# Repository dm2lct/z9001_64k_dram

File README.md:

# z9001_64k_dram
64kB RAM Modul für den Robotron KC87

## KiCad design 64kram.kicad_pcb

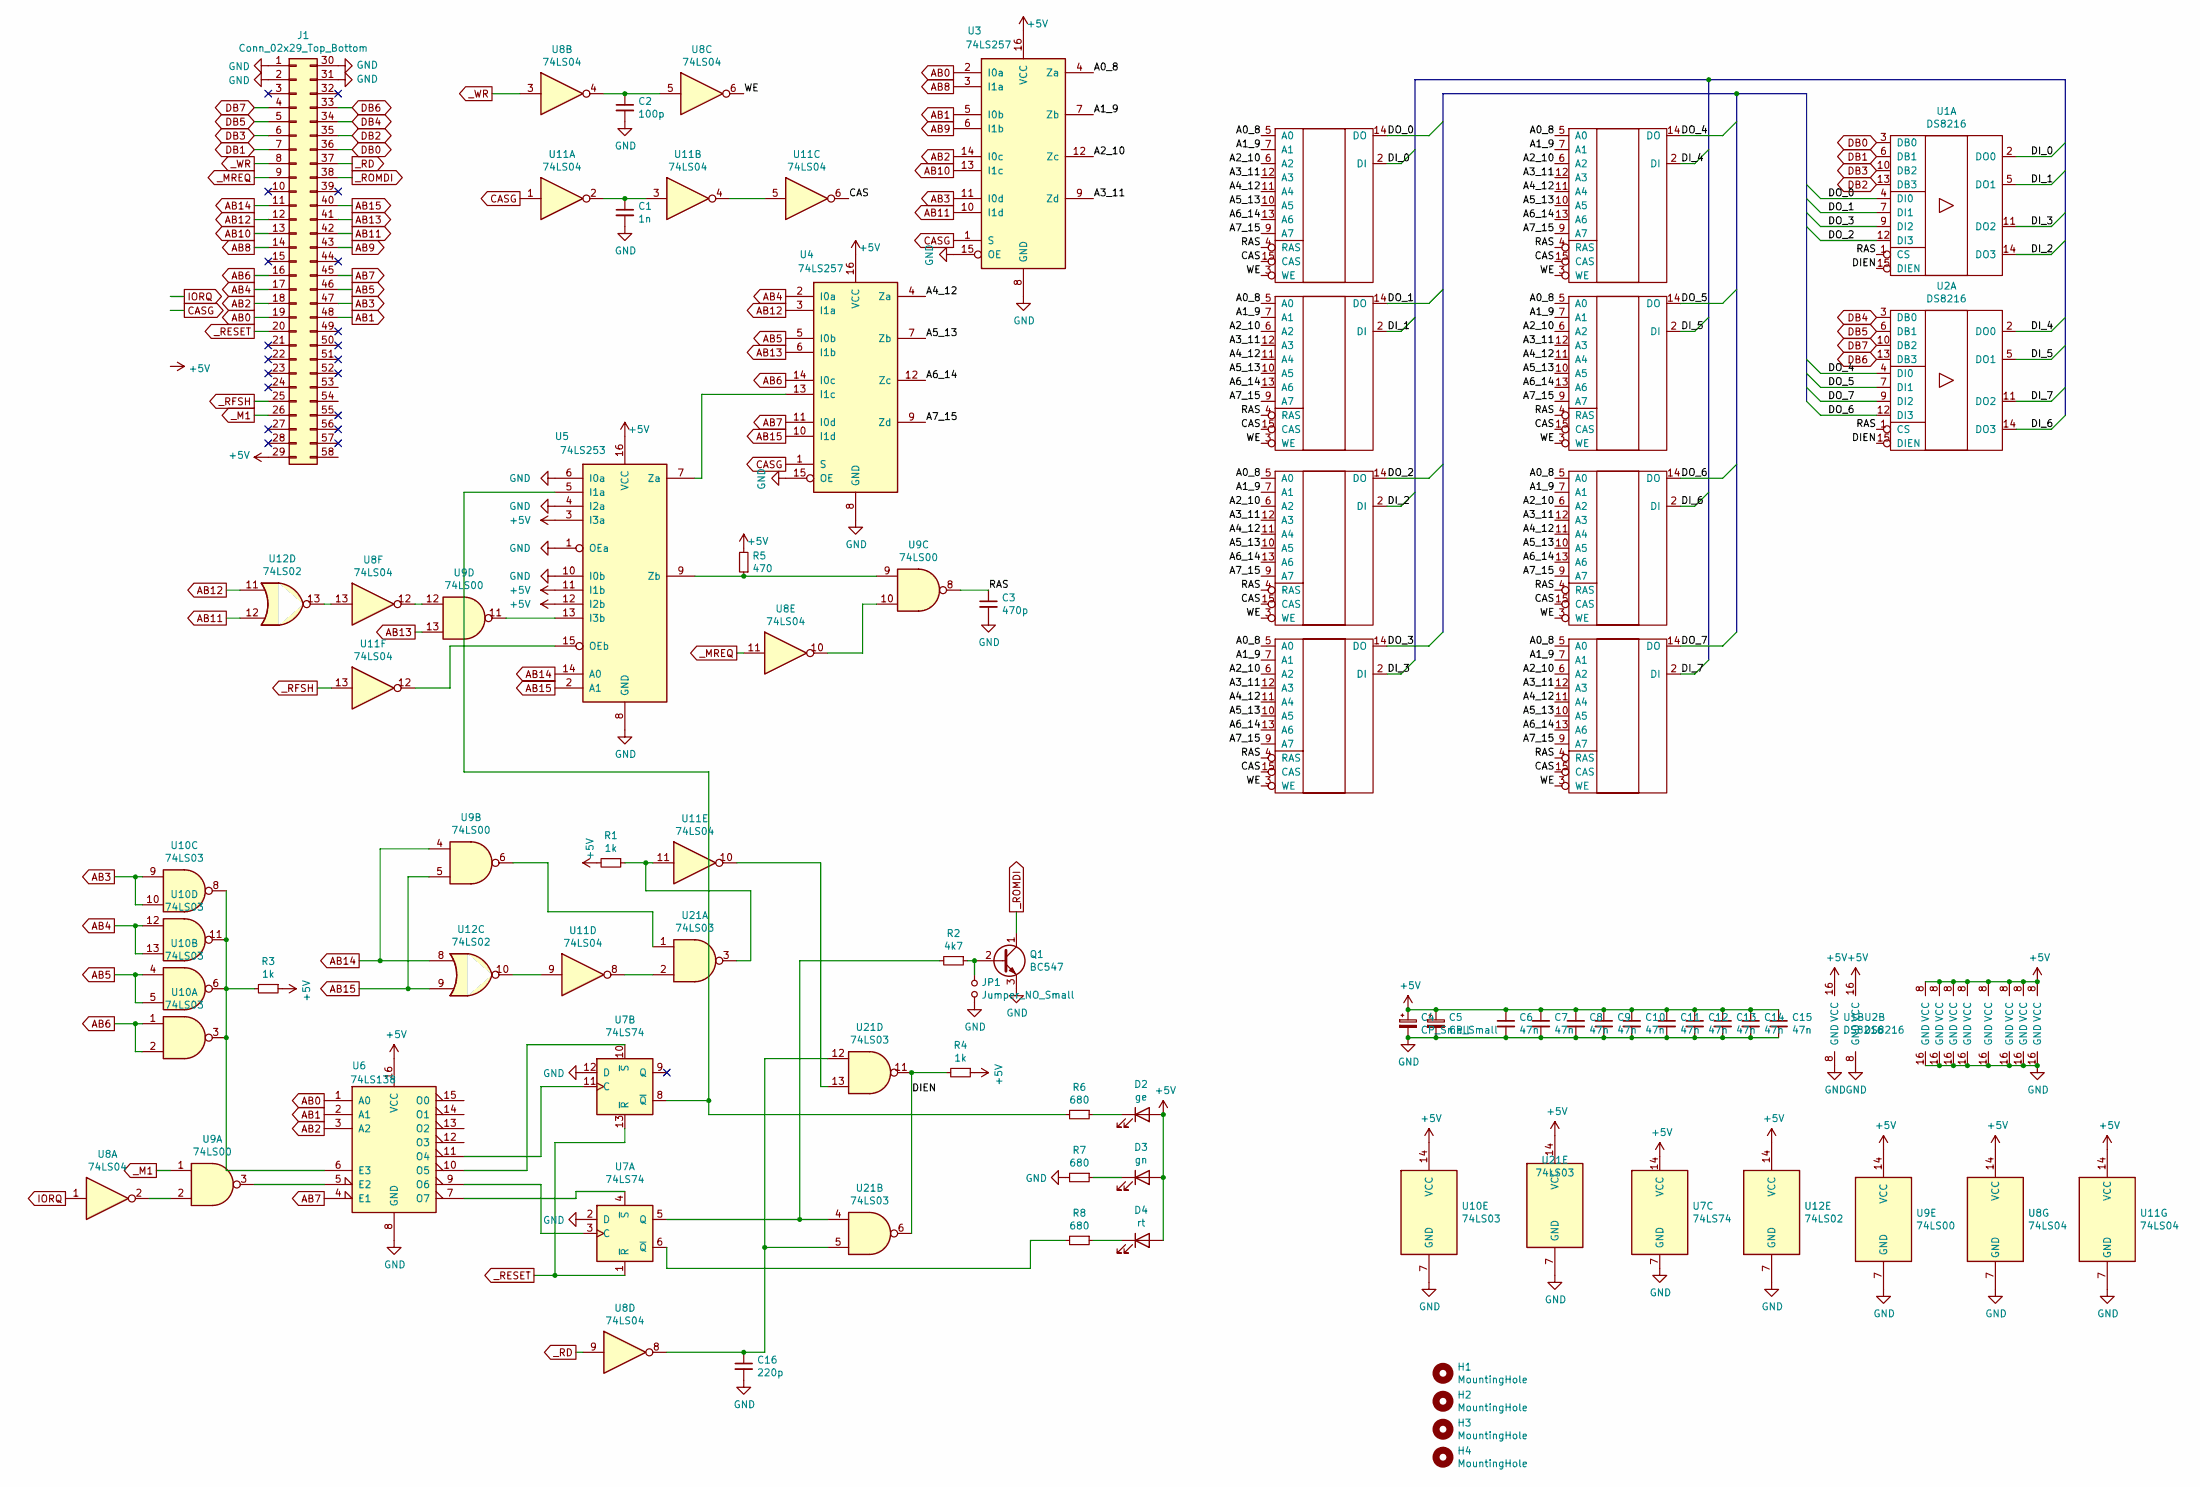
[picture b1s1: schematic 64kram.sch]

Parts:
C1: 1n; C_Disc_D4.3mm_W1.9mm_P5.00mm
C2: 100p; C_Disc_D4.3mm_W1.9mm_P5.00mm
C3: 470p; C_Disc_D4.3mm_W1.9mm_P5.00mm
C4, C5: CP_Small; CP_Axial_L11.0mm_D5.0mm_P18.00mm_Horizontal
C6, C7, C8, C9, C10, C11, C12, C13, C14, C15: 47n; C_Disc_D4.3mm_W1.9mm_P5.00mm
C16: 220p; C_Disc_D4.3mm_W1.9mm_P5.00mm
D2: ge; LED_D3.0mm
D3: gn; LED_D3.0mm
D4: rt; LED_D3.0mm
H1, H2, H3, H4: MountingHole; MountingHole_4.3mm_M4_DIN965
J1: Conn_02x29_Top_Bottom; EFS_58
JP1: Jumper_NO_Small; PinHeader_1x02_P2.54mm_Vertical
Q1: BC547; TO-92_Inline
R1, R3, R4: 1k; R_Axial_DIN0204_L3.6mm_D1.6mm_P7.62mm_Horizontal
R2: 4k7; R_Axial_DIN0204_L3.6mm_D1.6mm_P7.62mm_Horizontal
R5: 470; R_Axial_DIN0204_L3.6mm_D1.6mm_P7.62mm_Horizontal
R6, R7, R8: 680; R_Axial_DIN0204_L3.6mm_D1.6mm_P7.62mm_Horizontal
U1, U2: DS8216; DIP-16_W7.62mm
U3, U4: 74LS257; DIP-16_W7.62mm
U5: 74LS253; DIP-16_W7.62mm
U6: 74LS138; DIP-16_W7.62mm
U7: 74LS74; DIP-14_W7.62mm
U8, U11: 74LS04; DIP-14_W7.62mm
U9: 74LS00; DIP-14_W7.62mm
U10, U21: 74LS03; DIP-14_W7.62mm
U12: 74LS02; DIP-14_W7.62mm
U13, U14, U15, U16, U17, U18, U19, U20: U2164; DIP-16_W7.62mm

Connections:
+5V: C4.1, C5.1, C6.1, C7.1, C8.1, C9.1, C10.1, C11.1, C12.1, C13.1, C14.1, C15.1, D2.2 (A), D3.2 (A), D4.2 (A), J1.29, J1.58, R1.2, R3.1, R4.1, R5.2, U1.16 (VCC), U2.16 (VCC), U3.16 (VCC), U4.16 (VCC), U5.3 (I3a), U5.11 (I1b), U5.12 (I2b), U5.16 (VCC), U6.16 (VCC), U7.14 (VCC), U8.14 (VCC), U9.14 (VCC), U10.14 (VCC), U11.14 (VCC), U12.14 (VCC), U13.8 (VCC), U14.8 (VCC), U15.8 (VCC), U16.8 (VCC), U17.8 (VCC), U18.8 (VCC), U19.8 (VCC), U20.8 (VCC), U21.14 (VCC)
/A0_8: U3.4 (Za), U13.5 (A0), U14.5 (A0), U15.5 (A0), U16.5 (A0), U17.5 (A0), U18.5 (A0), U19.5 (A0), U20.5 (A0)
/A1_9: U3.7 (Zb), U13.7 (A1), U14.7 (A1), U15.7 (A1), U16.7 (A1), U17.7 (A1), U18.7 (A1), U19.7 (A1), U20.7 (A1)
/A2_10: U3.12 (Zc), U13.6 (A2), U14.6 (A2), U15.6 (A2), U16.6 (A2), U17.6 (A2), U18.6 (A2), U19.6 (A2), U20.6 (A2)
/A3_11: U3.9 (Zd), U13.12 (A3), U14.12 (A3), U15.12 (A3), U16.12 (A3), U17.12 (A3), U18.12 (A3), U19.12 (A3), U20.12 (A3)
/A4_12: U4.4 (Za), U13.11 (A4), U14.11 (A4), U15.11 (A4), U16.11 (A4), U17.11 (A4), U18.11 (A4), U19.11 (A4), U20.11 (A4)
/A5_13: U4.7 (Zb), U13.10 (A5), U14.10 (A5), U15.10 (A5), U16.10 (A5), U17.10 (A5), U18.10 (A5), U19.10 (A5), U20.10 (A5)
/A6_14: U4.12 (Zc), U13.13 (A6), U14.13 (A6), U15.13 (A6), U16.13 (A6), U17.13 (A6), U18.13 (A6), U19.13 (A6), U20.13 (A6)
/A7_15: U4.9 (Zd), U13.9 (A7), U14.9 (A7), U15.9 (A7), U16.9 (A7), U17.9 (A7), U18.9 (A7), U19.9 (A7), U20.9 (A7)
/CAS: U11.6, U13.15 (CAS), U14.15 (CAS), U15.15 (CAS), U16.15 (CAS), U17.15 (CAS), U18.15 (CAS), U19.15 (CAS), U20.15 (CAS)
/DIEN: R4.2, U1.15 (DIEN), U2.15 (DIEN), U21.6, U21.11
/DI_0: U1.2 (DO0), U13.2 (DI)
/DI_1: U1.5 (DO1), U14.2 (DI)
/DI_2: U1.14 (DO3), U15.2 (DI)
/DI_3: U1.11 (DO2), U16.2 (DI)
/DI_4: U2.2 (DO0), U17.2 (DI)
/DI_5: U2.5 (DO1), U18.2 (DI)
/DI_6: U2.14 (DO3), U19.2 (DI)
/DI_7: U2.11 (DO2), U20.2 (DI)
/DO_0: U1.4 (DI0), U13.14 (DO)
/DO_1: U1.7 (DI1), U14.14 (DO)
/DO_2: U1.12 (DI3), U15.14 (DO)
/DO_3: U1.9 (DI2), U16.14 (DO)
/DO_4: U2.4 (DI0), U17.14 (DO)
/DO_5: U2.7 (DI1), U18.14 (DO)
/DO_6: U2.12 (DI3), U19.14 (DO)
/DO_7: U2.9 (DI2), U20.14 (DO)
/RAS: C3.1, U1.1 (CS), U2.1 (CS), U9.8, U13.4 (RAS), U14.4 (RAS), U15.4 (RAS), U16.4 (RAS), U17.4 (RAS), U18.4 (RAS), U19.4 (RAS), U20.4 (RAS)
/WE: U8.6, U13.3 (WE), U14.3 (WE), U15.3 (WE), U16.3 (WE), U17.3 (WE), U18.3 (WE), U19.3 (WE), U20.3 (WE)
AB0: J1.19, U3.2 (I0a), U6.1 (A0)
AB1: J1.48, U3.5 (I0b), U6.2 (A1)
AB2: J1.18, U3.14 (I0c), U6.3 (A2)
AB3: J1.47, U3.11 (I0d), U10.9, U10.10
AB4: J1.17, U4.2 (I0a), U10.12, U10.13
AB5: J1.46, U4.5 (I0b), U10.4, U10.5
AB6: J1.16, U4.14 (I0c), U10.1, U10.2
AB7: J1.45, U4.11 (I0d), U6.4 (E1)
AB8: J1.14, U3.3 (I1a)
AB9: J1.43, U3.6 (I1b)
AB10: J1.13, U3.13 (I1c)
AB11: J1.42, U3.10 (I1d), U12.12
AB12: J1.12, U4.3 (I1a), U12.11
AB13: J1.41, U4.6 (I1b), U9.13
AB14: J1.11, U5.14 (A0), U9.4, U12.8
AB15: J1.40, U4.10 (I1d), U5.2 (A1), U9.5, U12.9
CASG: J1.54, U3.1 (S), U4.1 (S), U11.1
DB0: J1.36, U1.3 (DB0)
DB1: J1.7, U1.6 (DB1)
DB2: J1.35, U1.13 (DB3)
DB3: J1.6, U1.10 (DB2)
DB4: J1.34, U2.3 (DB0)
DB5: J1.5, U2.6 (DB1)
DB6: J1.33, U2.13 (DB3)
DB7: J1.4, U2.10 (DB2)
GND: C1.2, C2.2, C3.2, C4.2, C5.2, C6.2, C7.2, C8.2, C9.2, C10.2, C11.2, C12.2, C13.2, C14.2, C15.2, C16.2, J1.1, J1.2, J1.30, J1.31, JP1.2, Q1.3 (E), R7.2, U1.8 (GND), U2.8 (GND), U3.8 (GND), U3.15 (OE), U4.8 (GND), U4.15 (OE), U5.1 (OEa), U5.4 (I2a), U5.6 (I0a), U5.8 (GND), U5.10 (I0b), U6.8 (GND), U7.2 (D), U7.7 (GND), U7.12 (D), U8.7 (GND), U9.7 (GND), U10.7 (GND), U11.7 (GND), U12.7 (GND), U13.16 (GND), U14.16 (GND), U15.16 (GND), U16.16 (GND), U17.16 (GND), U18.16 (GND), U19.16 (GND), U20.16 (GND), U21.7 (GND)
IORQ: J1.53, U8.1
unnamed: C1.1, U11.2, U11.3
unnamed: C2.1, U8.4, U8.5
unnamed: C16.1, U8.8, U21.5, U21.12
unnamed: D2.1 (K), R6.1
unnamed: D3.1 (K), R7.1
unnamed: D4.1 (K), R8.1
unnamed: JP1.1, Q1.2 (B), R2.1
unnamed: R1.1, U11.11, U21.3
unnamed: R2.2, U7.5 (Q), U21.4
unnamed: R3.2, U6.6 (E3), U10.3, U10.6, U10.8, U10.11
unnamed: R5.1, U5.9 (Zb), U9.9
unnamed: R6.2, U5.5 (I1a), U7.8 (~Q)
unnamed: R8.2, U7.6 (~Q)
unnamed: U4.13 (I1c), U5.7 (Za)
unnamed: U5.13 (I3b), U9.11
unnamed: U6.5 (E2), U9.3
unnamed: U6.7 (O7), U7.4 (~S)
unnamed: U6.9 (O6), U7.3 (C)
unnamed: U6.10 (O5), U7.10 (~S)
unnamed: U6.11 (O4), U7.11 (C)
unnamed: U8.2, U9.2
unnamed: U8.10, U9.10
unnamed: U8.12, U9.12
unnamed: U11.4, U11.5
unnamed: U11.8, U21.2
unnamed: U11.9, U12.10
unnamed: U11.10, U21.13
unnamed: U5.15 (OEb), U11.12
unnamed: U8.13, U12.13
unnamed: U9.6, U21.1
_M1: J1.26, U9.1
_MREQ: J1.9, U8.11
_RD: J1.37, U8.9
_RESET: J1.20, U7.1 (~R), U7.13 (~R)
_RFSH: J1.25, U11.13
_ROMDI: J1.38, Q1.1 (C)
_WR: J1.8, U8.3

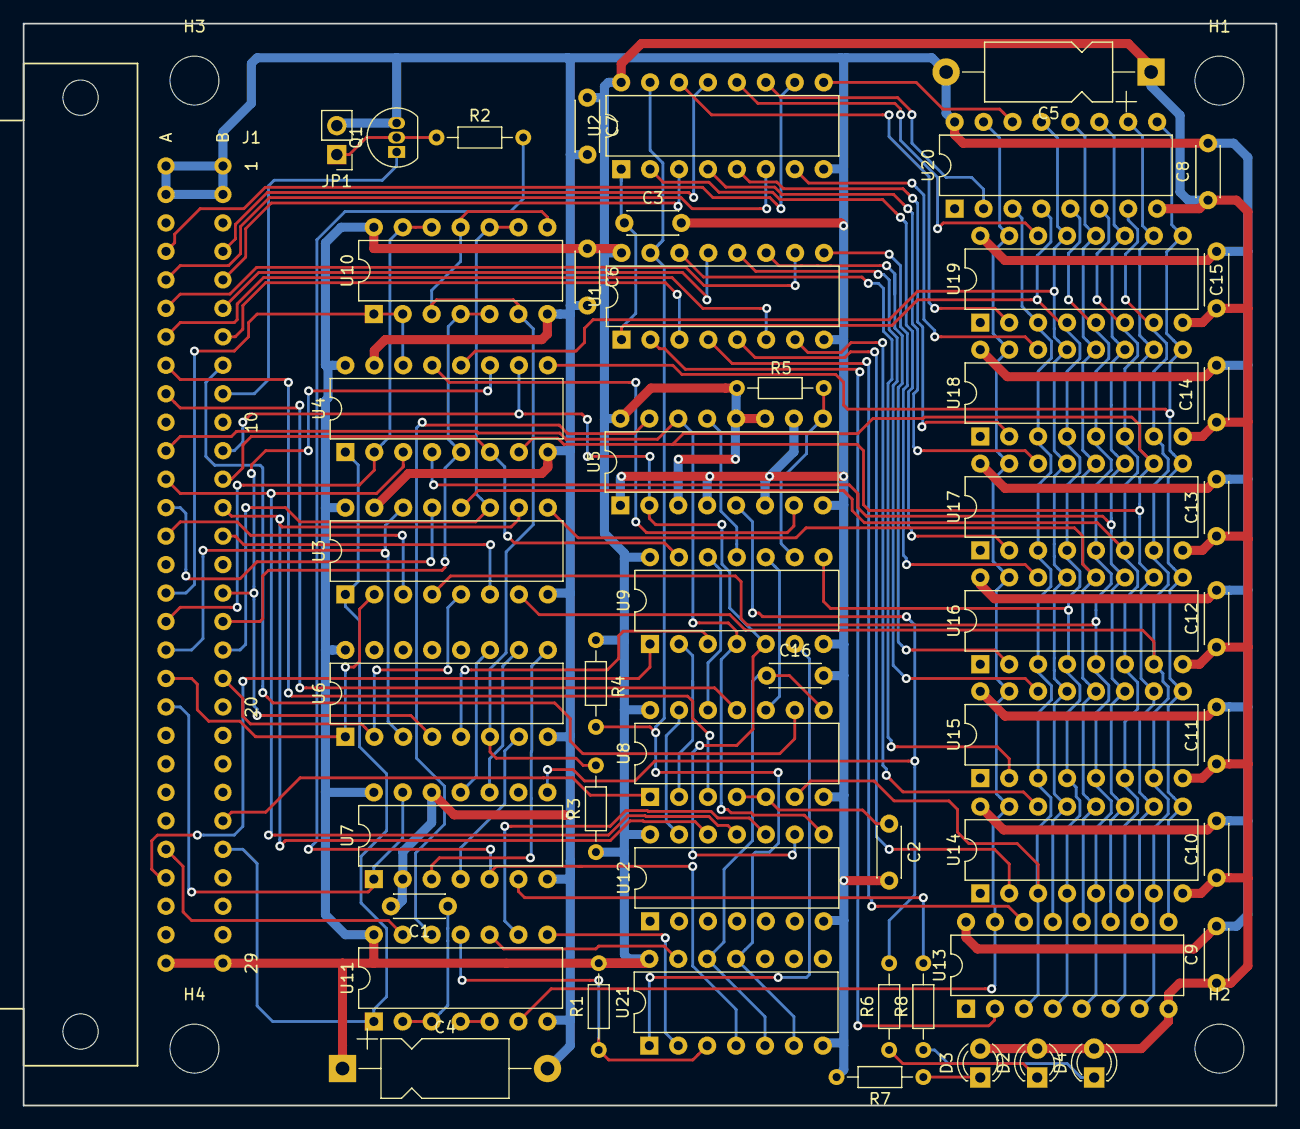
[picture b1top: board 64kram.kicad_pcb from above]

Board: 2 copper layers, 110.0 x 95.0 mm, 55 parts (0 on the bottom side), 93 nets.
